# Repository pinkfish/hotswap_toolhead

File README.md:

# hotswap_toolhead (USB version)

A small USB toolhead board for 3D printers. It reads a thermistor (100k NTC or PT1000) and a switch, and drives a 5 V fan (0.3 A or less). Everything comes over one USB-C cable. It runs Klipper over USB on an STM32G0B1.

The heater is not on this board: it is wired straight to the printer's mainboard on its own cable.

- **Board:** one 18 × 23.5 mm, 4-layer board, no mounting holes (hold it in a printed pocket or clip).
- **Plugs:** USB-C on the top edge. A 6-pin JST-SH (1 mm pitch) on the bottom edge carries fan, thermistor and switch.
- **Power:** USB VBUS (5 V) feeds a 3.3 V LDO for the logic, and the fan through a PTC.
- **Other branches:** `usb-only` is the first version of this board (22 × 30 mm, JST-PH plug, M2.5 holes). `stack` is the 24 V CAN version: two stacked 27 × 27 mm boards with a 100 W heater output. `narrow-27` and `centre-j2` are the single-board 24 V versions.

## Repository layout

| Folder | Contents |
| --- | --- |
| `docs/` | Design spec (`design_spec.md`), with the Klipper config |
| `hardware/` | KiCad project `toolhead_usb`: schematic, routed PCB, design rules, JLCPCB BOM. `panel/`, `panel6/` and `panel4/` are the panels to order |
| `gerber/` | Fab outputs. `usb/` is the single board, for checking. `panel/` (9 boards), `panel6/` (6) and `panel4/` (4) are what you order: see `gerber/README.md` |
| `tools/` | See below |

What's in `tools/`:

- `design.py`: the netlist.
- `gen_kicad.py`: builds the schematic, BOM and rules from it.
- `verify.py`: checks every pin's net.
- `fab.sh`: regenerates `gerber/usb/`.
- `make_panel.sh`: builds the panels.
- `layout/`: the placement and routing scripts (see `tools/layout/README.md`).

## Status

The schematic is complete and the PCB is routed:

- DRC: 0 errors, 0 unconnected, schematic parity clean.
- All three panels build with 0 DRC errors.

Nothing has been built or tested yet. Before relying on it, read "Heater on the mainboard" in `docs/design_spec.md`: a Klipper heater with its sensor on a different MCU hasn't been tried.

## Regenerating the KiCad files

```
python3 tools/gen_kicad.py   # rebuilds hardware/toolhead_usb.kicad_sch, BOM and rules from tools/design.py
python3 tools/verify.py      # re-parses the schematic and checks every pin's net
```

The generator never touches the routed board. After a netlist change, choose one:

- Run **Update PCB from Schematic** in KiCad and fix up the routing.
- Re-run the layout (`tools/layout/run_usb.sh`).

Then run `tools/fab.sh` and `tools/make_panel.sh` (9, 6 and 4).

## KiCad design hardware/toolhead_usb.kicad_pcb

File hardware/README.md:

# USB toolhead board – KiCad project

`tools/gen_kicad.py` generates the schematic from `tools/design.py`, the netlist. The PCB is routed. The project opens in KiCad 8 or newer; it was routed and checked in KiCad 10.

## What's here

| File | Contents |
| --- | --- |
| `toolhead_usb.kicad_pro` | The project file: open this in KiCad. Netclasses: Fan 0.4 / 0.3 mm, Supply and USB 0.3 / 0.2 mm |
| `toolhead_usb.kicad_sch` | Schematic: 40 parts. Blocks: logic supply, MCU, USB, the plug, fan, thermistor, switch |
| `toolhead_usb.kicad_pcb` | The routed board: 18 × 23.5 mm, 4 layers, no mounting holes |
| `toolhead_usb.kicad_dru` | Custom design rules: USB pair, and the fan current's minimum track width |
| `toolhead_usb-bom-jlcpcb.csv`, `bom_jlcpcb.csv` | The BOM in JLCPCB's upload format (the two are the same). The PT1000 and BOOT pads (JP2, JP3) are left out; every other part is placed |
| `panel/`, `panel6/`, `panel4/` | The panels to order: 9, 6 or 4 boards, built by `../tools/make_panel.sh` |
| `fp-lib-table`, `footprints/` | Project footprint library, left over from the 24 V boards; the USB board uses only KiCad's standard libraries |

`tools/verify.py` re-parses the schematic and rebuilds the netlist from pin and label positions. Every pin matches `tools/design.py`, and no pin is left dangling.

## Layout

| Layer | What's on it |
| --- | --- |
| F.Cu | J5 (USB-C), J2 (JST-SH), SW1, LED1/LED2 with R5/R6, the fan driver (Q3, D5, R15, R16), R17–R19, C19 and D6, R22, R23 and C20; GND pour |
| In1 | Solid GND |
| In2 | Signals and +3V3 |
| B.Cu | U6 with Y1, FB1 and C9, C11–C15; U5 and C17 under J5, C10 above U5; R20/R21; F2; JP2; JP3 with R4; U1 with C4 and C8; GND pour |

- **Reference designators:** most bottom-side ones are on B.Fab rather than the silkscreen, because there is no room for them. They still appear on assembly drawings.

## Check against datasheets

- **U1 (ME6211C33M5G-N):** pins 1 VIN, 2 GND, 3 CE, 4 NC, 5 VOUT. CE is tied to VIN.
- **J2 (JST SM06B-SRSS-TB):** pin 1 is at the left, seen from the top with the plug opening at the bottom edge. Check against the cable's housing before crimping:
  - 1 FAN+
  - 2 FAN−
  - 3 TH_SIG
  - 4 thermistor GND
  - 5 SENS
  - 6 GND
- **U6 STM32G0B1 pinout:** VREF+ 5, VDD/VDDA 6, VSS/VSSA 7, PB12/PB13 24/25, PA11/12 33/34, PA14/PA15 36/37, PB8 47. Confirm against ST DS13560.
- **Crystal Y1:** 20 pF load with 33 pF caps. Check the oscillator's gain margin (ST AN2867) on the first board.

## Net names

| Net | What it is |
| --- | --- |
| `VBUS` | USB 5 V |
| `+3V3` | The LDO's output |
| `VREFP` | The ferrite-filtered ADC reference and thermistor pull-up |
| `FAN_P` | The fan + after F2 |
| `FAN_N` | Q3's drain |
| `TH_SIG` | The thermistor |
| `TH_ADC` | The filtered ADC input |
| `SENS` / `SENS_IN` | The switch, before and after its filter |

## Fab outputs

`../tools/fab.sh` exports `../gerber/usb/` with `kicad-cli`: 4-layer gerbers, drill files, the BOM and the CPL. `tools/jlc_cpl.py` writes the CPL by fitting each part's own JLCPCB footprint onto its pads. The panels are in `../gerber/panel*/`. `../gerber/README.md` says which files to upload.

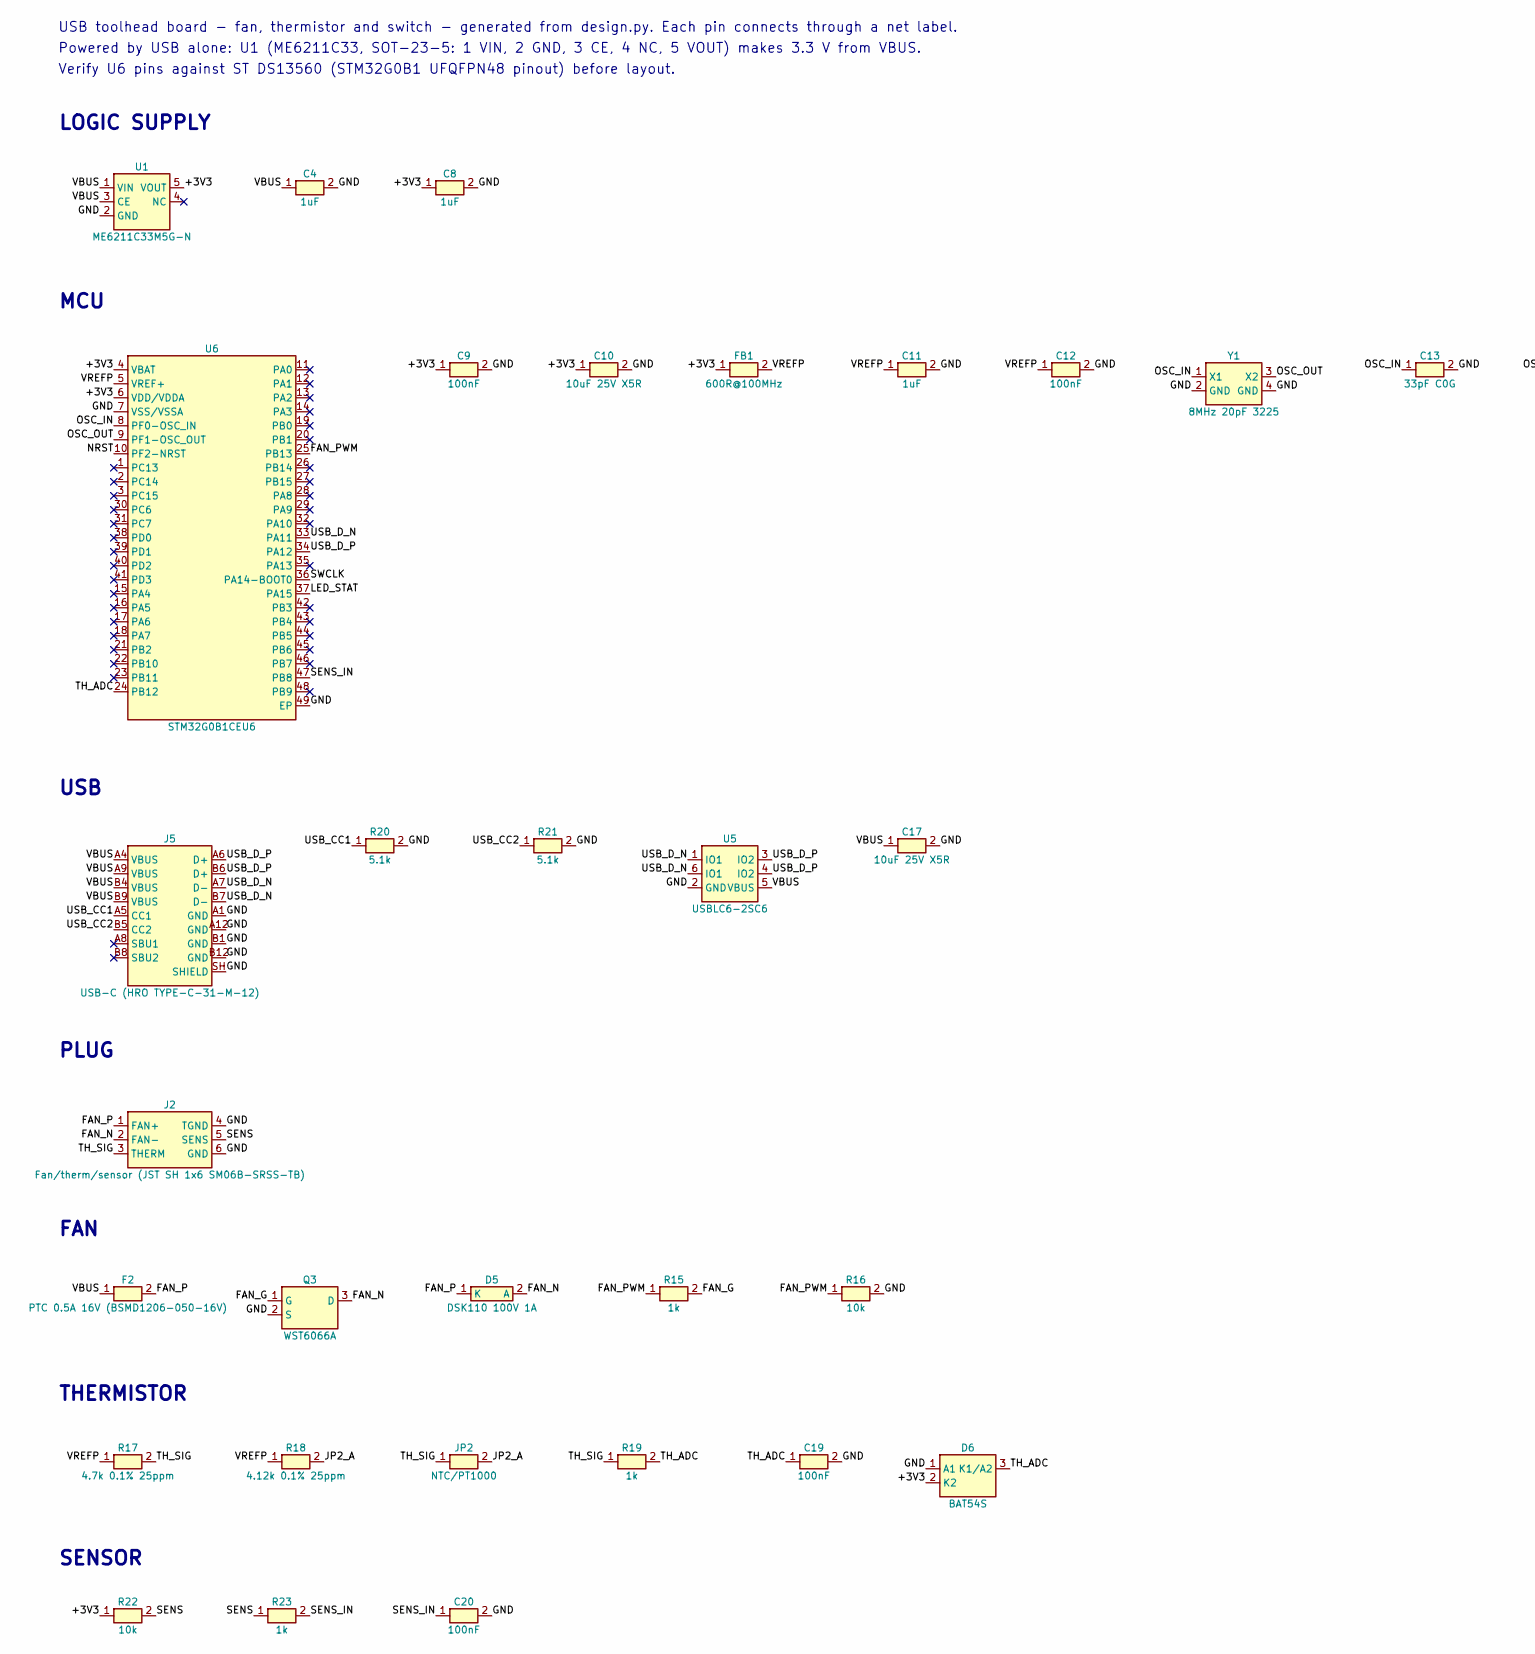
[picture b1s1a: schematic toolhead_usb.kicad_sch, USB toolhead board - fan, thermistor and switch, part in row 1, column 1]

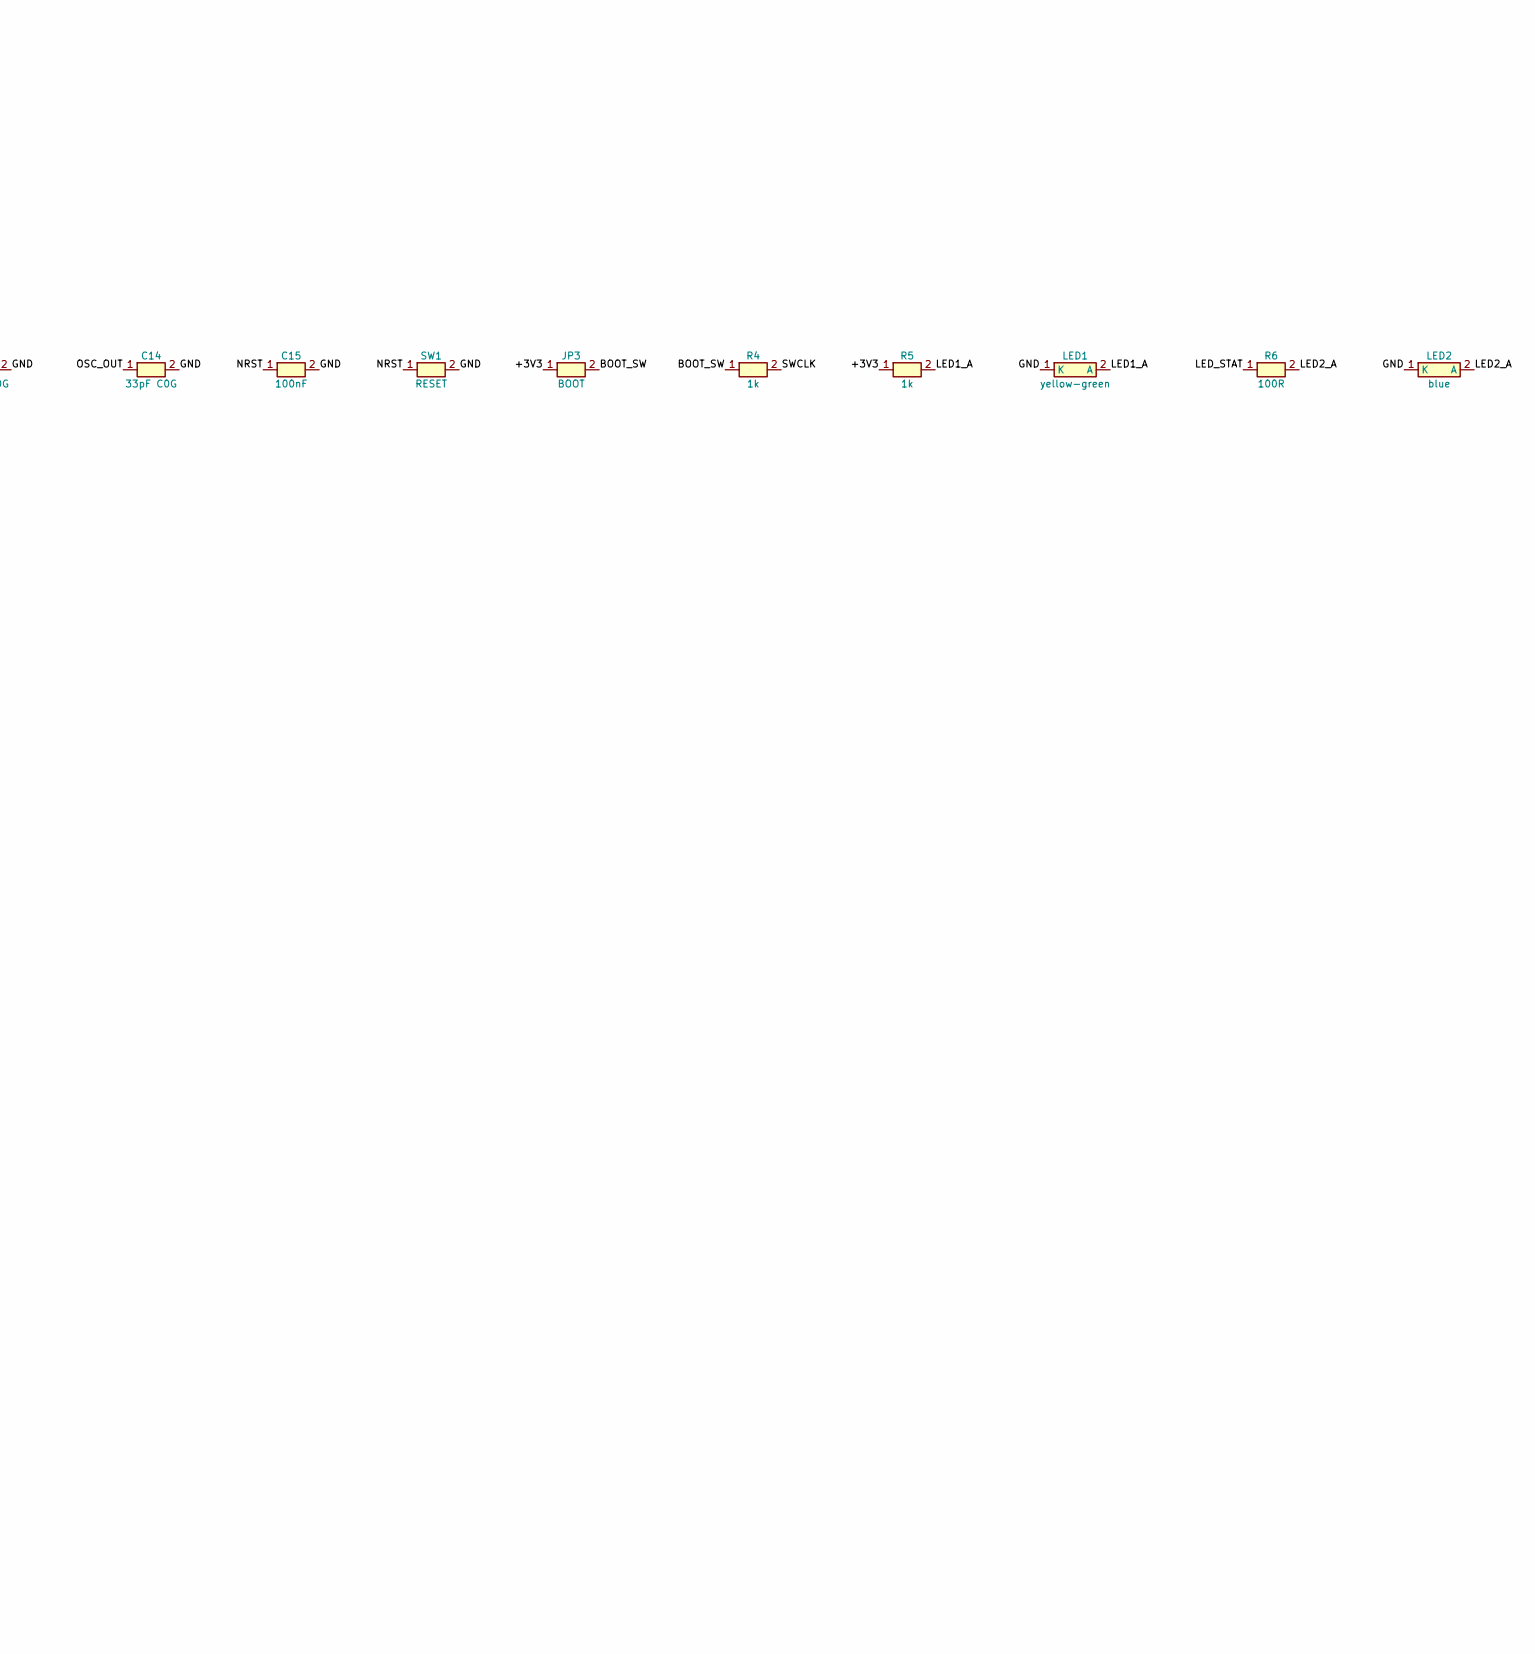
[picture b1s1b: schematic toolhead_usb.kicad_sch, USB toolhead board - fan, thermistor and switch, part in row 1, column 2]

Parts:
C4, C8, C11: 1uF; C_0402_1005Metric; LCSC C52923
C9, C12, C15, C19, C20: 100nF; C_0402_1005Metric; LCSC C1525
C10, C17: 10uF 25V X5R; C_0805_2012Metric; LCSC C15850
C13, C14: 33pF C0G; C_0402_1005Metric; LCSC C1562
D5: DSK110 100V 1A; D_SOD-123F; LCSC C22466354
D6: BAT54S; SOT-23; LCSC C7420333
F2: PTC 0.5A 16V (BSMD1206-050-16V); Fuse_1206_3216Metric; LCSC C883124
FB1: 600R@100MHz; L_0402_1005Metric; LCSC C76884
J2: Fan/therm/sensor (JST SH 1x6 SM06B-SRSS-TB); JST_SH_SM06B-SRSS-TB_1x06-1MP_P1.00mm_Horizontal; LCSC C160405
J5: USB-C (HRO TYPE-C-31-M-12); USB_C_Receptacle_HRO_TYPE-C-31-M-12; LCSC C165948
JP2: NTC/PT1000; SolderJumper-2_P1.3mm_Open_RoundedPad1.0x1.5mm
JP3: BOOT; SolderJumper-2_P1.3mm_Open_RoundedPad1.0x1.5mm
LED1: yellow-green; LED_0603_1608Metric; LCSC C2289
LED2: blue; LED_0603_1608Metric; LCSC C2288
Q3: WST6066A; SOT-23; LCSC C148352
R4, R5, R15, R19, R23: 1k; R_0402_1005Metric; LCSC C11702
R6: 100R; R_0402_1005Metric; LCSC C25076
R16, R22: 10k; R_0402_1005Metric; LCSC C25744
R17: 4.7k 0.1% 25ppm; R_0402_1005Metric; LCSC C281778
R18: 4.12k 0.1% 25ppm; R_0402_1005Metric; LCSC C852812
R20, R21: 5.1k; R_0402_1005Metric; LCSC C25905
SW1: RESET; SW_SPST_EVQP7C; LCSC C388883
U1: ME6211C33M5G-N; SOT-23-5; LCSC C82942
U5: USBLC6-2SC6; SOT-23-6; LCSC C7519
U6: STM32G0B1CEU6; QFN-48-1EP_7x7mm_P0.5mm_EP5.6x5.6mm; LCSC C2829190
Y1: 8MHz 20pF 3225; Crystal_SMD_3225-4Pin_3.2x2.5mm; LCSC C2682774

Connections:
/+3V3: C8.1, C9.1, C10.1, D6.2 (K2), FB1.1, JP3.1, R5.1, R22.1, U1.5 (VOUT), U6.4 (VBAT), U6.6 (VDD/VDDA)
/BOOT_SW: JP3.2, R4.1
/FAN_G: Q3.1 (G), R15.2
/FAN_N: D5.2 (A), J2.2 (FAN-), Q3.3 (D)
/FAN_P: D5.1 (K), F2.2, J2.1 (FAN+)
/FAN_PWM: R15.1, R16.1, U6.25 (PB13)
/GND: C4.2, C8.2, C9.2, C10.2, C11.2, C12.2, C13.2, C14.2, C15.2, C17.2, C19.2, C20.2, D6.1 (A1), J2.4 (TGND), J2.6 (GND), J5.A1 (GND), J5.A12 (GND), J5.B1 (GND), J5.B12 (GND), J5.SH (SHIELD), LED1.1 (K), LED2.1 (K), Q3.2 (S), R16.2, R20.2, R21.2, SW1.2, U1.2 (GND), U5.2 (GND), U6.7 (VSS/VSSA), U6.49 (EP), Y1.2 (GND), Y1.4 (GND)
/JP2_A: JP2.2, R18.2
/LED1_A: LED1.2 (A), R5.2
/LED2_A: LED2.2 (A), R6.2
/LED_STAT: R6.1, U6.37 (PA15)
/NRST: C15.1, SW1.1, U6.10 (PF2-NRST)
/OSC_IN: C13.1, U6.8 (PF0-OSC_IN), Y1.1 (X1)
/OSC_OUT: C14.1, U6.9 (PF1-OSC_OUT), Y1.3 (X2)
/SENS: J2.5 (SENS), R22.2, R23.1
/SENS_IN: C20.1, R23.2, U6.47 (PB8)
/SWCLK: R4.2, U6.36 (PA14-BOOT0)
/TH_ADC: C19.1, D6.3 (K1/A2), R19.2, U6.24 (PB12)
/TH_SIG: J2.3 (THERM), JP2.1, R17.2, R19.1
/USB_CC1: J5.A5 (CC1), R20.1
/USB_CC2: J5.B5 (CC2), R21.1
/USB_D_N: J5.A7 (D-), J5.B7 (D-), U5.1 (IO1), U5.6 (IO1), U6.33 (PA11)
/USB_D_P: J5.A6 (D+), J5.B6 (D+), U5.3 (IO2), U5.4 (IO2), U6.34 (PA12)
/VBUS: C4.1, C17.1, F2.1, J5.A4 (VBUS), J5.A9 (VBUS), J5.B4 (VBUS), J5.B9 (VBUS), U1.1 (VIN), U1.3 (CE), U5.5 (VBUS)
/VREFP: C11.1, C12.1, FB1.2, R17.1, R18.1, U6.5 (VREF+)

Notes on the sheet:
LOGIC SUPPLY
MCU
USB
PLUG
FAN
THERMISTOR
SENSOR
USB toolhead board - fan, thermistor and switch - generated from design.py. Each pin connects through a net label.
Powered by USB alone: U1 (ME6211C33, SOT-23-5: 1 VIN, 2 GND, 3 CE, 4 NC, 5 VOUT) makes 3.3 V from VBUS.
Verify U6 pins against ST DS13560 (STM32G0B1 UFQFPN48 pinout) before layout.

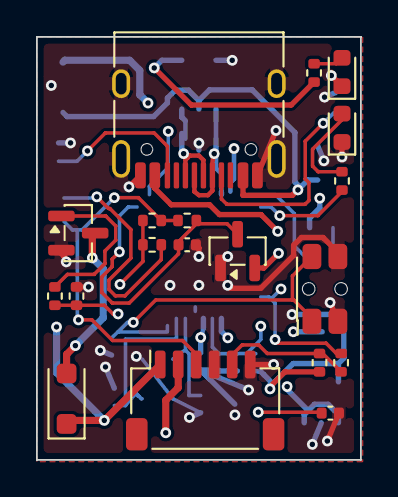
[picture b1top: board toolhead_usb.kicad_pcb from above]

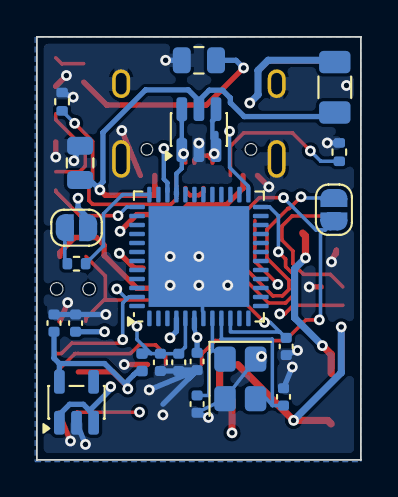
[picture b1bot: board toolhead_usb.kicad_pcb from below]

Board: 4 copper layers, 18.0 x 23.5 mm, 40 parts (21 on the bottom side), 25 nets.

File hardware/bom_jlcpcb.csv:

Comment,Designator,Footprint,LCSC Part #
100R,R6,R_0402_1005Metric,C25076
100nF,"C9,C12,C15,C19,C20",C_0402_1005Metric,C1525
10k,"R16,R22",R_0402_1005Metric,C25744
10uF 25V X5R,"C10,C17",C_0805_2012Metric,C15850
1k,"R4,R5,R15,R19,R23",R_0402_1005Metric,C11702
1uF,"C4,C8,C11",C_0402_1005Metric,C52923
33pF C0G,"C13,C14",C_0402_1005Metric,C1562
4.12k 0.1% 25ppm,R18,R_0402_1005Metric,C852812
4.7k 0.1% 25ppm,R17,R_0402_1005Metric,C281778
5.1k,"R20,R21",R_0402_1005Metric,C25905
600R@100MHz,FB1,L_0402_1005Metric,C76884
8MHz 20pF 3225,Y1,Crystal_SMD_3225-4Pin_3.2x2.5mm,C2682774
BAT54S,D6,SOT-23,C7420333
DSK110 100V 1A,D5,D_SOD-123F,C22466354
Fan/therm/sensor (JST SH 1x6 SM06B-SRSS-TB),J2,JST_SH_SM06B-SRSS-TB_1x06-1MP_P1.00mm_Horizontal,C160405
ME6211C33M5G-N,U1,SOT-23-5,C82942
PTC 0.5A 16V (BSMD1206-050-16V),F2,Fuse_1206_3216Metric,C883124
RESET,SW1,SW_SPST_EVQP7C,C388883
STM32G0B1CEU6,U6,QFN-48-1EP_7x7mm_P0.5mm_EP5.6x5.6mm,C2829190
USB-C (HRO TYPE-C-31-M-12),J5,USB_C_Receptacle_HRO_TYPE-C-31-M-12,C165948
USBLC6-2SC6,U5,SOT-23-6,C7519
WST6066A,Q3,SOT-23,C148352
blue,LED2,LED_0603_1608Metric,C2288
yellow-green,LED1,LED_0603_1608Metric,C2289

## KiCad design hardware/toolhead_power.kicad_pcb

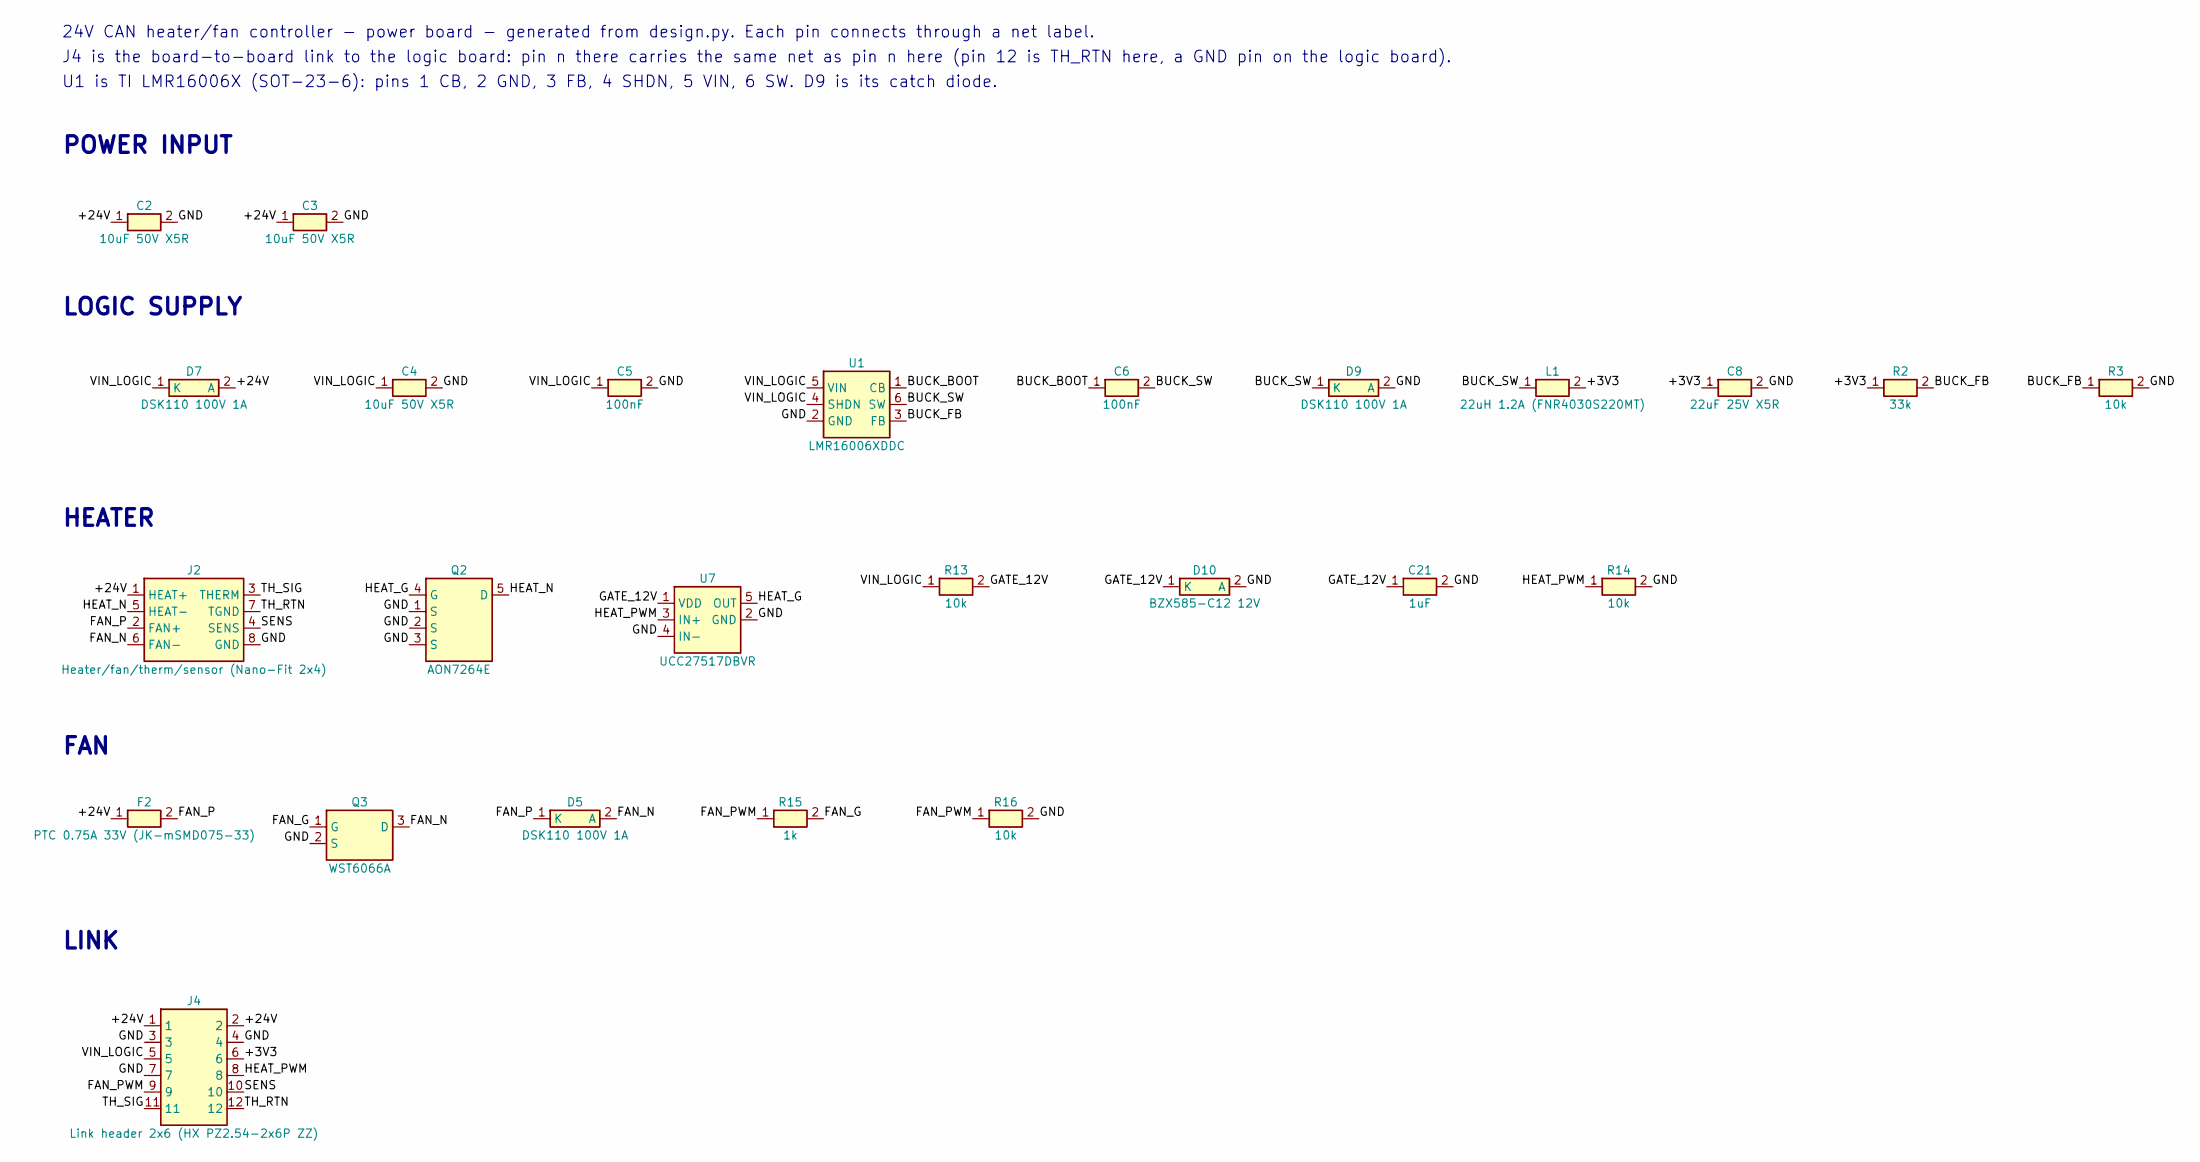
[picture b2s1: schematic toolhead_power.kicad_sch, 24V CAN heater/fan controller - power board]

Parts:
C2, C3, C4: 10uF 50V X5R; C_1206_3216Metric; LCSC C13585
C5: 100nF; C_0603_1608Metric; LCSC C14663
C6: 100nF; C_0402_1005Metric; LCSC C1525
C8: 22uF 25V X5R; C_1206_3216Metric; LCSC C12891
C21: 1uF; C_0402_1005Metric; LCSC C52923
D5, D7, D9: DSK110 100V 1A; D_SOD-123F; LCSC C22466354
D10: BZX585-C12 12V; D_SOD-523; LCSC C455018
F2: PTC 0.75A 33V (JK-mSMD075-33); Fuse_1812_4532Metric; LCSC C369169
J2: Heater/fan/therm/sensor (Nano-Fit 2x4); Molex_Nano-Fit_105314-xx08_2x04_P2.50mm_Horizontal; LCSC C841208
J4: Link header 2x6 (HX PZ2.54-2x6P ZZ); PinHeader_2x06_P2.54mm_Vertical; LCSC C32713279
L1: 22uH 1.2A (FNR4030S220MT); L_Taiyo-Yuden_NR-40xx; LCSC C167883
Q2: AON7264E; AOS_DFN-8-1EP_3x3mm_P0.65mm; LCSC C431191
Q3: WST6066A; SOT-23; LCSC C148352
R2: 33k; R_0402_1005Metric; LCSC C25779
R3, R13, R14, R16: 10k; R_0402_1005Metric; LCSC C25744
R15: 1k; R_0402_1005Metric; LCSC C11702
U1: LMR16006XDDC; SOT-23-6; LCSC C87080
U7: UCC27517DBVR; SOT-23-5; LCSC C99395

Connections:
/+3V3: C8.1, J4.6, L1.2, R2.1
/+24V: C2.1, C3.1, D7.2 (A), F2.1, J2.1 (HEAT+), J4.1, J4.2
/BUCK_BOOT: C6.1, U1.1 (CB)
/BUCK_FB: R2.2, R3.1, U1.3 (FB)
/BUCK_SW: C6.2, D9.1 (K), L1.1, U1.6 (SW)
/FAN_G: Q3.1 (G), R15.2
/FAN_N: D5.2 (A), J2.6 (FAN-), Q3.3 (D)
/FAN_P: D5.1 (K), F2.2, J2.2 (FAN+)
/FAN_PWM: J4.9, R15.1, R16.1
/GATE_12V: C21.1, D10.1 (K), R13.2, U7.1 (VDD)
/GND: C2.2, C3.2, C4.2, C5.2, C8.2, C21.2, D9.2 (A), D10.2 (A), J2.8 (GND), J4.3, J4.4, J4.7, Q2.1 (S), Q2.2 (S), Q2.3 (S), Q3.2 (S), R3.2, R14.2, R16.2, U1.2 (GND), U7.2 (GND), U7.4 (IN-)
/HEAT_G: Q2.4 (G), U7.5 (OUT)
/HEAT_N: J2.5 (HEAT-), Q2.5 (D)
/HEAT_PWM: J4.8, R14.1, U7.3 (IN+)
/SENS: J2.4 (SENS), J4.10
/TH_RTN: J2.7 (TGND), J4.12
/TH_SIG: J2.3 (THERM), J4.11
/VIN_LOGIC: C4.1, C5.1, D7.1 (K), J4.5, R13.1, U1.4 (SHDN), U1.5 (VIN)

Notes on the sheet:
POWER INPUT
LOGIC SUPPLY
HEATER
FAN
LINK
24V CAN heater/fan controller - power board - generated from design.py. Each pin connects through a net label.
J4 is the board-to-board link to the logic board: pin n there carries the same net as pin n here (pin 12 is TH_RTN here, a GND pin on the logic board).
U1 is TI LMR16006X (SOT-23-6): pins 1 CB, 2 GND, 3 FB, 4 SHDN, 5 VIN, 6 SW. D9 is its catch diode.

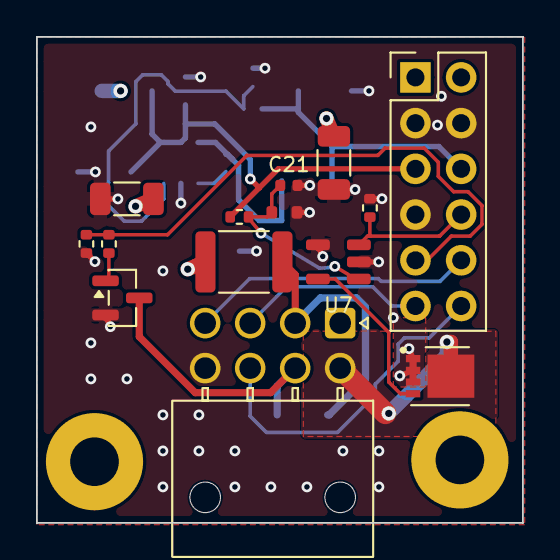
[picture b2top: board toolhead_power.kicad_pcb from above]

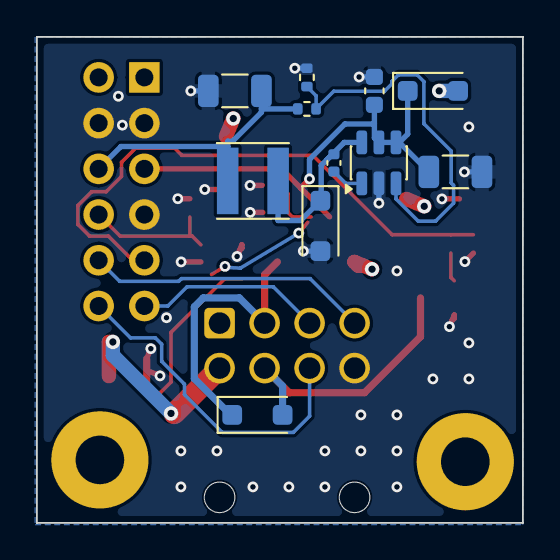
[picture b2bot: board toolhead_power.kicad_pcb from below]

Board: 4 copper layers, 27.0 x 27.0 mm, 27 parts (11 on the bottom side), 18 nets.

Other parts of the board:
H1, H2: M2.5 isolated; MountingHole_2.7mm_M2.5_Pad

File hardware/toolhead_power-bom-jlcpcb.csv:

Comment,Designator,Footprint,LCSC Part #
100nF,C6,C_0402_1005Metric,C1525
100nF,C5,C_0603_1608Metric,C14663
10k,"R3,R13,R14,R16",R_0402_1005Metric,C25744
10uF 50V X5R,"C2,C3,C4",C_1206_3216Metric,C13585
1k,R15,R_0402_1005Metric,C11702
1uF,C21,C_0402_1005Metric,C52923
22uF 25V X5R,C8,C_1206_3216Metric,C12891
22uH 1.2A (FNR4030S220MT),L1,L_Taiyo-Yuden_NR-40xx,C167883
33k,R2,R_0402_1005Metric,C25779
AON7264E,Q2,AOS_DFN-8-1EP_3x3mm_P0.65mm,C431191
BZX585-C12 12V,D10,D_SOD-523,C455018
DSK110 100V 1A,"D5,D7,D9",D_SOD-123F,C22466354
Heater/fan/therm/sensor (Nano-Fit 2x4),J2,Molex_Nano-Fit_105314-xx08_2x04_P2.50mm_Horizontal,C841208
LMR16006XDDC,U1,SOT-23-6,C87080
Link header 2x6 (HX PZ2.54-2x6P ZZ),J4,PinHeader_2x06_P2.54mm_Vertical,C32713279
PTC 0.75A 33V (JK-mSMD075-33),F2,Fuse_1812_4532Metric,C369169
UCC27517DBVR,U7,SOT-23-5,C99395
WST6066A,Q3,SOT-23,C148352

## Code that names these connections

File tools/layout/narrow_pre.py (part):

"""narrow_pre.py board.kicad_pcb - pre-routes for the 27 mm board (run_narrow.sh).
FAN_P: F2's output reaches the fan clamp D5, under J2, round the right-hand end of J2's pin rows: down
from F2 pad 2 on F.Cu to a via right of J2 pin 1, then on B.Cu down the lane between J2's pins
and L1 and across to D5 pad 1. The 31 mm board's via was where Q2 now is; between J2's pins
there's no room (0.8 mm gaps), and the HEAT_N pour takes the lane on top.
D7's +24V via: up-left of its pad as on the 31 mm board (BUCK_FB runs between D7's pads, and
U6 pin 48's escape takes the room below), replacing the block copper's.
LED_STAT: from U6 pin 44 up to a via above D7's, then on F.Cu down its left to R6.
HEAT_PWM, NRST: kept from crossing east of U6 (U7 is below that, SW1 above); NRST above C8.
VREFP: out of its decoupling to the right and back left on F.Cu between C8 and F2.
LED1_A, LED2_A: R6 left, R5 right, so the anodes go up the right of the LEDs without crossing;
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route(F, f2a, (f2a[0], vf[1] - 0.34), vf, net='/+24V', w=0.8)
via('/+24V', vf, 0.8, 0.4)

# HEAT_PWM and NRST, which would cross east of U6: HEAT_PWM from pin 48 on B.Cu to a via below R6,
# clear of D7 and U1, then on F.Cu down to U7; NRST above C8 and under the LED resistors to SW1
for t in list(b.GetTracks()):
    if t.GetNetname() == '/HEAT_PWM':
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route(F, v1, (v1[0] + 0.35, v1[1] + 0.35), (v1[0] + 0.35, v2[1] - 1.5), v2, net='/+3V3', w=0.25)
route(B, v2, (v2[0] + 0.2, v2[1] + 0.2), (l12[0], v2[1] + 0.2), l12, net='/+3V3', w=0.25)

# FAN_PWM to R15 on the left edge has to cross the CAN pair coming down from J1: from U6 pin 17
# on B.Cu to a via left of C1, then on F.Cu up and along the strip below J1 to R15. CAN_L drops
# to B.Cu at the end of its F.Cu run from J1, above the strip, so the two don't cross on F.Cu.
p17, r15 = at('U6', '17'), at('R15', '1')
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
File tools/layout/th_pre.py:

"""th_pre.py board.kicad_pcb th|pwm - pre-route TH_ADC from U6 pin 14 to R19/C19 (th), or HEAT_PWM (pwm).
U6's ADC pins face left, but the thermistor filter sits below the crystal and Q2, which wall
it off on top (Q2, HEAT_N) and bottom (crystal cluster).  TH_ADC stays on B.Cu: out of the
pin above SENS_IN's escape, down the lane between J2's heater pins and C15/C14 (needs C15 at
corner_pre's shifted spot for the 0.3 mm 24 V clearance to J2), then along y 29.37 under the
crystal to R19.
Also pre-routes HEAT_PWM from U6 pin 48's escape via to R13 and R14 on F.Cu, which the
autorouters kept leaving open.
'th' runs before sig_fanout (SENS_IN's escape then keeps clear of the lane); 'pwm' after it
(needs the pin 48 via); both before planes_fanout (GND vias move round them).
"""
import sys, pcbnew
mm = pcbnew.FromMM
b = pcbnew.LoadBoard(sys.argv[1]); O = 100.0
F, B = pcbnew.F_Cu, pcbnew.B_Cu
P = lambda x, y: pcbnew.VECTOR2I(mm(O + x), mm(O + y))
net = b.FindNet('/TH_ADC')
p14 = [p for p in b.FindFootprintByReference('U6').Pads() if p.GetNumber() == '14'][0].GetPosition()
x0, y0 = pcbnew.ToMM(p14.x) - O, pcbnew.ToMM(p14.y) - O


def tr(layer, *pts):
    for a, c in zip(pts, pts[1:]):
        t = pcbnew.PCB_TRACK(b); t.SetStart(P(*a)); t.SetEnd(P(*c)); t.SetWidth(mm(0.2))
        t.SetLayer(layer); t.SetNet(net); t.SetLocked(True); b.Add(t)


r19 = [p for p in b.FindFootprintByReference('R19').Pads() if p.GetNetname() == '/TH_ADC'][0].GetPosition()
c19 = [p for p in b.FindFootprintByReference('C19').Pads() if p.GetNetname() == '/TH_ADC'][0].GetPosition()
mmx = lambda q: (pcbnew.ToMM(q.x) - O, pcbnew.ToMM(q.y) - O)
rx, ry = mmx(r19)
MODE = sys.argv[2]
# all on B.Cu: out of pin 14 above SENS_IN's stub and via, down the lane, under the crystal
if MODE == 'th':
    tr(B, (x0, y0), (12.25, y0), (11.9, y0 + 0.35), (11.9, 29.0), (12.27, 29.37), (rx - 0.6, 29.37), (rx, 29.97), (rx, ry), mmx(c19))
if MODE == 'th':
    pcbnew.SaveBoard(sys.argv[1], b)
    print('TH_ADC pre-routed from pin 14 at %.2f %.2f' % (x0, y0))
    sys.exit()
hv = [t for t in b.GetTracks() if t.GetClass() == 'PCB_VIA' and t.GetNetname() == '/HEAT_PWM']
assert len(hv) == 1, 'expected one HEAT_PWM escape via'
hx, hy = mmx(hv[0].GetPosition())
r13 = mmx([p for p in b.FindFootprintByReference('R13').Pads() if p.GetNetname() == '/HEAT_PWM'][0].GetPosition())
r14 = mmx([p for p in b.FindFootprintByReference('R14').Pads() if p.GetNetname() == '/HEAT_PWM'][0].GetPosition())
net = b.FindNet('/HEAT_PWM')
# R13/R14 stand upright with their HEAT_PWM pads in a row: across from the via to R14, on to R13
tr(F, (hx, hy), (hx - abs(hy - r14[1]), r14[1]), r14, r13)
pcbnew.SaveBoard(sys.argv[1], b)
print('HEAT_PWM pre-routed from via at %.2f %.2f' % (hx, hy))

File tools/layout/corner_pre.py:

"""Hand layout of the U6 pin 4-10 corner (crystal, load caps, decoupling, VREF), before routing.
    corner_pre.py board.kicad_pcb
Same cluster as rev A's routed board, shifted with U6: parts placed with pad 1 up/down,
+3V3 pins 4 and 6 dropped to staggered vias so VREFP (pin 5) runs straight down between
them, and GND pin 7 tied into the exposed pad. VREFP's long run to R17 starts here too.
"""
import sys

import pcbnew

mm = pcbnew.FromMM
b = pcbnew.LoadBoard(sys.argv[1])
OX = OY = 100.0
FP = {f.GetReference(): f for f in b.GetFootprints()}
u6 = FP['U6']
DX = pcbnew.ToMM(u6.GetPosition().x) - OX - 16.3
DY = pcbnew.ToMM(u6.GetPosition().y) - OY - 23.6
PLACE = {
    'Y1': (14.0, 30.4, 270),
    'C9': (16.4, 29.43, 'up'),
    'C11': (17.42, 29.48, 'up'),
    'C12': (18.44, 29.48, 'up'),
    'FB1': (19.46, 29.48, 'down'),     # pad 2 (VREFP) on top, in line with C11/C12
    'C13': (16.4, 31.8, 'up'),
    'C14': (11.6, 31.4, 'down'),       # GND pad up, so it can tie to C15's (TH_ADC boxes it in below)
    'C15': (11.45, 28.6, 'up'),        # 0.3 right of rev A: opens the TH_ADC lane by J2
}
PIN_VIAS = {'6': (16.4, 28.2), '4': (17.75, 28.15)}
KNEE_Y = 27.6


def P(x, y):
    return pcbnew.VECTOR2I(mm(OX + x + DX), mm(OY + y + DY))


def pad(f, n):
    return [p for p in f.Pads() if p.GetNumber() == n][0]


def track(net, a, c, w):
    t = pcbnew.PCB_TRACK(b)
    t.SetStart(a)
    t.SetEnd(c)
    t.SetWidth(mm(w))
    t.SetLayer(pcbnew.B_Cu)
    t.SetNet(net)
    t.SetLocked(True)
    b.Add(t)


for ref, (x, y, rot) in PLACE.items():
    f = FP[ref]
    f.SetPosition(P(x, y))
    if rot in ('up', 'down'):
        best = None
        for a in (0, 90, 180, 270):
            f.SetOrientationDegrees(a)
            key = pad(f, '1').GetPosition().y * (1 if rot == 'up' else -1)
            if best is None or key < best[0]:
                best = (key, a)
        rot = best[1]
    f.SetOrientationDegrees(rot)

p7, ep = pad(u6, '7'), pad(u6, '49')
c7 = p7.GetPosition()
track(p7.GetNet(), c7, pcbnew.VECTOR2I(c7.x, ep.GetBoundingBox().GetBottom() - mm(0.2)), 0.2)
for num, (x, y) in PIN_VIAS.items():
    p = pad(u6, num)
    pos = P(x, y)
    knee = pcbnew.VECTOR2I(p.GetPosition().x, P(0, KNEE_Y).y)
    track(p.GetNet(), p.GetPosition(), knee, 0.25)
    track(p.GetNet(), knee, pos, 0.25)
    v = pcbnew.PCB_VIA(b)
    v.SetPosition(pos)
    v.SetWidth(mm(0.6))
    v.SetDrill(mm(0.3))
    v.SetNet(p.GetNet())
    v.SetLocked(True)
    b.Add(v)
# U6 pins 8-10 (OSC_IN, OSC_OUT, NRST) pre-routed so none boxes another in: NRST hugs the
# pin row out to C15, OSC_OUT runs under it and round the left of Y1's GND pad 4 to pad 3
# and C14, OSC_IN drops straight to Y1 pad 1 and on down the right side to C13.  Pad 4 is
# then enclosed, so it ties diagonally across the crystal to GND pad 2.
y1 = FP['Y1']


def R(*pts, net, w=0.2):
    pts = [pcbnew.VECTOR2I(mm(OX + x), mm(OY + y)) for x, y in pts]
    for a, c in zip(pts, pts[1:]):
        track(b.FindNet(net), a, c, w)


def at(f, n):
    q = pad(f, n).GetPosition()
    return pcbnew.ToMM(q.x) - OX, pcbnew.ToMM(q.y) - OY


def box(f, n):
    r = pad(f, n).GetBoundingBox()
    return [pcbnew.ToMM(v) - o for v, o in ((r.GetX(), OX), (r.GetY(), OY), (r.GetRight(), OX), (r.GetBottom(), OY))]


x8, yp = at(u6, '8')
x9, _ = at(u6, '9')
x10, _ = at(u6, '10')
row = box(u6, '9')[3]                      # pin row bottom edge
c15, c14, c13 = at(FP['C15'], '1'), at(FP['C14'], '1'), at(FP['C13'], '1')
p4 = box(y1, '4')                          # GND pad nearest the pins, left
p1 = box(y1, '1')                          # OSC_IN pad, right
q3 = at(y1, '3')
xl = p4[0] - 0.33
yo = row + 0.72
R((x10, yp), (x10, row + 0.32), (c15[0] + 0.35, row + 0.32), c15, net='/NRST')
R((x9, yp), (x9, yo), (xl, yo), (xl, c14[1]), c14, net='/OSC_OUT')
R((xl, c14[1]), (q3[0] - 0.35, q3[1] - 0.3), net='/OSC_OUT')
xr = p1[2] + 0.3
R((x8, yp), (x8, p1[1] + 0.2), (p1[2] - 0.25, p1[1] + 0.4), net='/OSC_IN')
R((x8, p1[1] + 0.2), (xr, p1[1] + 0.4), (xr, c13[1]), c13, net='/OSC_IN')
R(at(y1, '4'), at(y1, '2'), net='/GND')
# TH_ADC's lane (left_pre) closes off the GND pads under the crystal: tie them to neighbours with vias
R(at(FP['C14'], '2'), at(FP['C15'], '2'), net='/GND')
g = at(FP['C14'], '2'); g = (g[0] - 0.1, g[1] - 0.35)   # that pair is boxed in too: via on C14's pad edge, clear of TH_ADC's via and D6
gv = pcbnew.PCB_VIA(b)
gv.SetPosition(pcbnew.VECTOR2I(mm(OX + g[0]), mm(OY + g[1])))
gv.SetWidth(mm(0.6))
gv.SetDrill(mm(0.3))
gv.SetNet(b.FindNet('/GND'))
gv.SetLocked(True)
b.Add(gv)
R(at(y1, '2'), at(FP['C13'], '2'), net='/GND')
# VREFP's exit towards the thermistor pull-up (R17, far left): the C11/C12/FB1 row is closed
# in above by the pin vias and below by the GND/+3V3 pads, so it leaves round the east side
# of FB1 and drops on B.Cu to below the row; the router takes it on from there
fb, f1 = at(FP['FB1'], '2'), box(FP['FB1'], '1')
xe = f1[2] + 0.36
R(fb, (xe, fb[1]), (xe, f1[3] + 0.13), (fb[0] + 0.14, f1[3] + 0.54), (fb[0] + 0.14, f1[3] + 1.2), net='/VREFP')
# that loop closes in FB1's +3V3 pad: it gets its own via, just below and to the left
fp1 = at(FP['FB1'], '1')
vv = (fp1[0] - 0.46, f1[3] + 0.6)
R(fp1, (fp1[0] - 0.2, f1[3] + 0.2), vv, net='/+3V3')
v = pcbnew.PCB_VIA(b)
v.SetPosition(pcbnew.VECTOR2I(mm(OX + vv[0]), mm(OY + vv[1])))
v.SetWidth(mm(0.6))
v.SetDrill(mm(0.3))
v.SetNet(b.FindNet('/+3V3'))
v.SetLocked(True)
b.Add(v)
pcbnew.SaveBoard(sys.argv[1], b)
print('corner placed, shift %.2f %.2f' % (DX, DY))
